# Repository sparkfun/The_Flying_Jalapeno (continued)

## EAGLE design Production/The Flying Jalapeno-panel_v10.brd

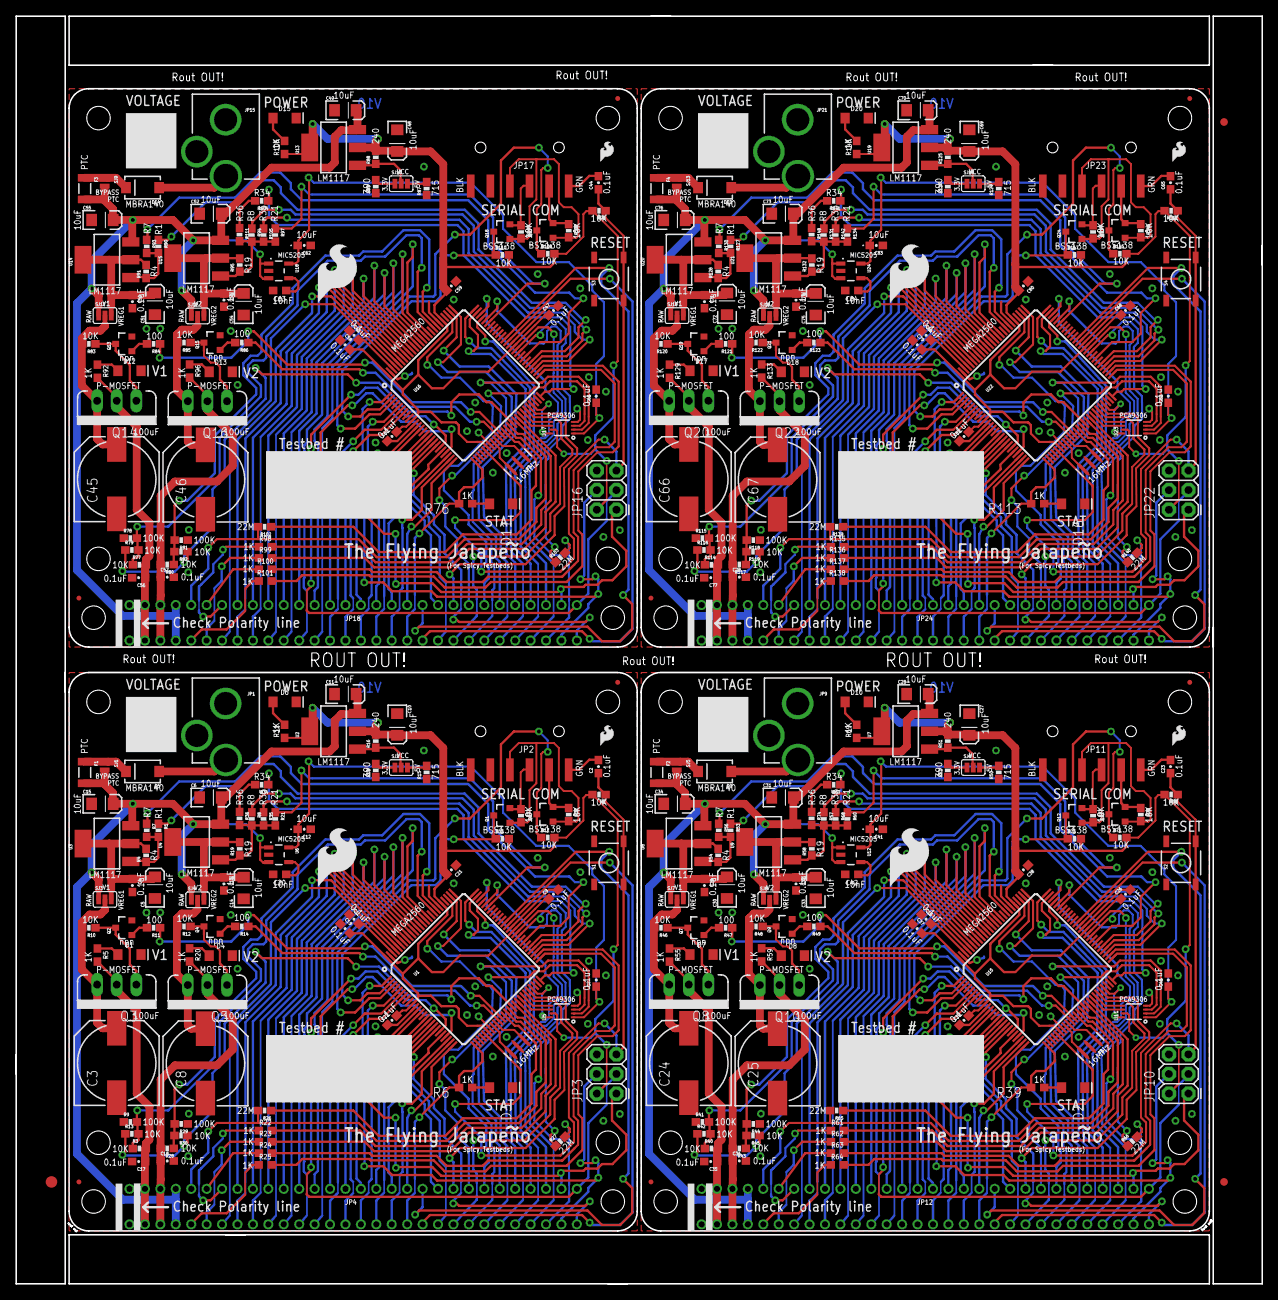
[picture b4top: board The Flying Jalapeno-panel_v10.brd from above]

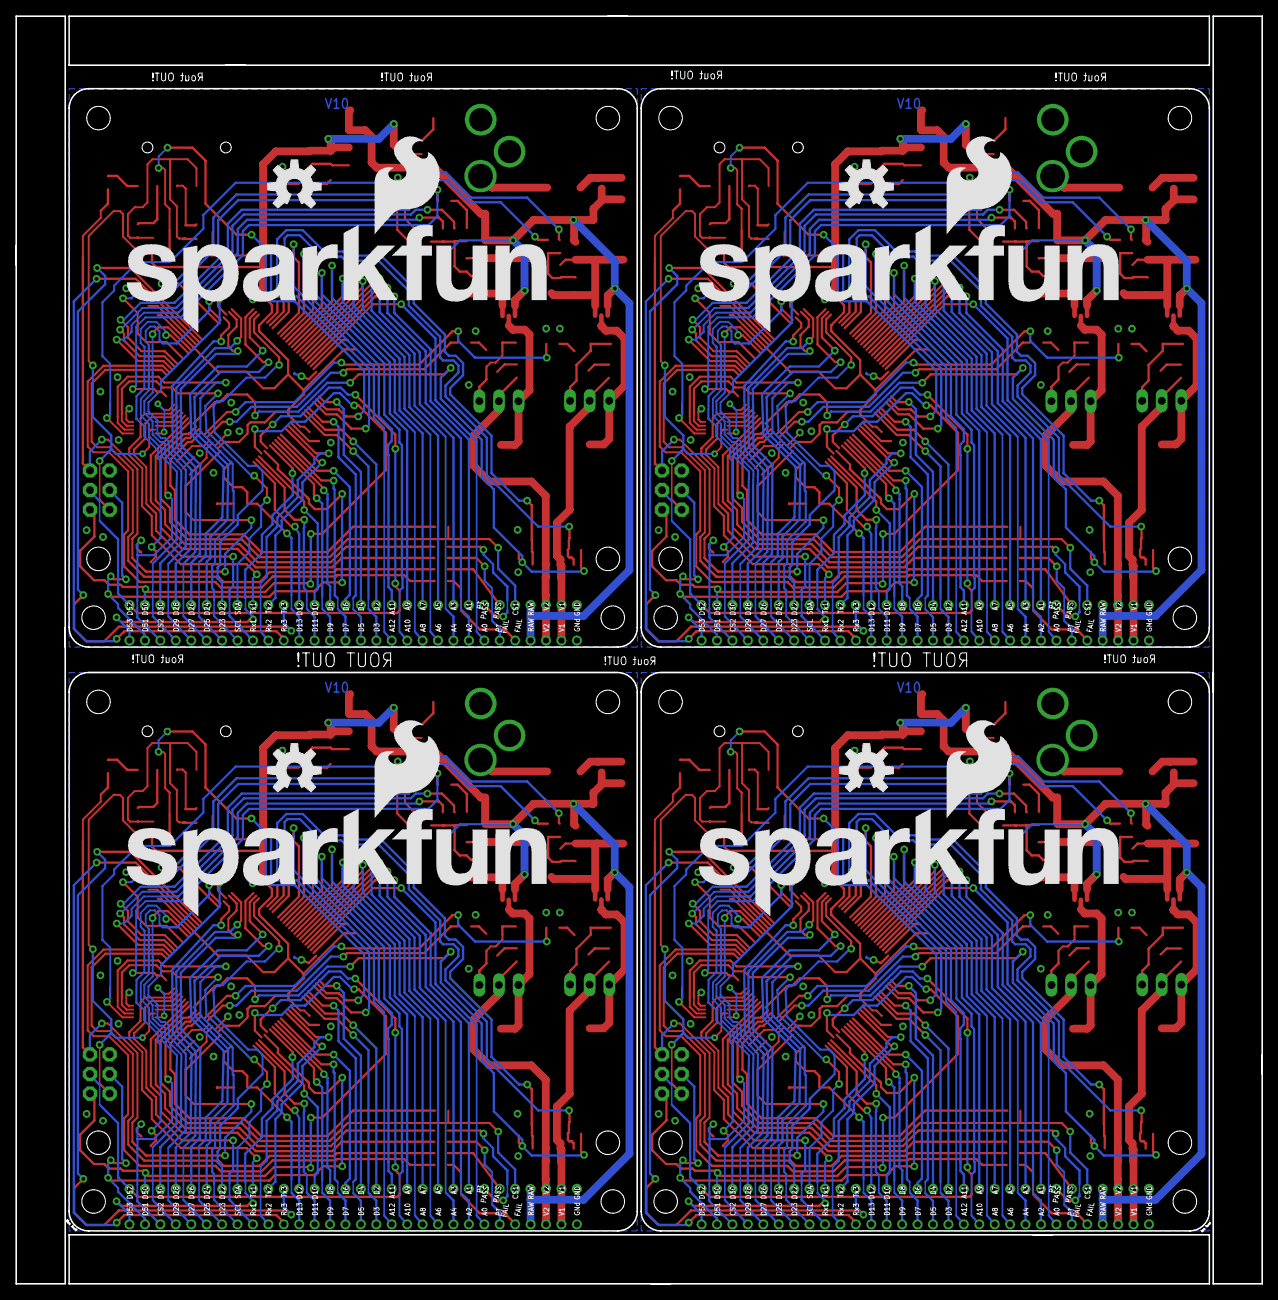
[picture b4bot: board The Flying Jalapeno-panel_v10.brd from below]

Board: 2 copper layers, 161.5 x 164.3 mm, 387 parts (8 on the bottom side), 436 nets.

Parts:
C1, C2, C4, C7, C9, C13, C16, C17, C18, C19, C21, C22, C23, C26, C29, C32, C35, C36, C37, C38, C39, C40, C43, C44, C47, C50, C53, C56, C57, C58, C59, C60, C61, C64, C65, C68, C71, C74, C77, C78, C79, C80, C81, C82: 0.1uF; 0603-CAP
C3, C8, C24, C25, C45, C46, C66, C67: 100uF; NIC_10X10.5_CAP
C5, C6, C10, C11, C14, C15, C27, C28, C30, C31, C33, C34, C48, C49, C51, C52, C54, C55, C69, C70, C72, C73, C75, C76: 10uF; EIA3216
C12, C41, C62, C83: 10uF; 0603-POL
C20, C42, C63, C84: 10nF; 0603
D1, D2, D3, D4, D6, D7, D8, D10, D11, D12, D13, D15, D16, D17, D18, D20: RED; LED-1206
D5, D9, D14, D19: MBRA140; SMA-DIODE
E$1: FIDUCIAL-1.5X3
E$7, E$8: FIDUCIAL-1X2
F1, F2, F3, F4: PTC-1206
JP1, JP9, JP15, JP21: 7V; POWER_JACK_PTH_LOCK
JP2, JP11, JP17, JP23: FTDI; FTDI_DEVICE_RA_SMT
JP3, JP10, JP16, JP22: 2X3
JP4, JP12, JP18, JP24: 2x30 RA FEMALE HEADER; FLYING_JALAPENO_V2_F
JP5, JP6, JP7, JP8, JP13, JP14, JP19, JP20: FIDUCIALUFIDUCIAL; MICRO-FIDUCIAL
LOGO1, LOGO5, LOGO9, LOGO13: SFE_LOGO_NAME_FLAME.5_INCH; SFE_LOGO_NAME_FLAME_.5
LOGO2, LOGO8, LOGO12, LOGO16: SFE_LOGO_FLAME.3_INCH; SFE_LOGO_FLAME_.3
LOGO3, LOGO6, LOGO10, LOGO14: SFE_LOGO_FLAME.1_INCH; SFE_LOGO_FLAME_.1
LOGO4, LOGO7, LOGO11, LOGO15: OSHW-LOGOL; OSHW-LOGO-L
Q1, Q6, Q11, Q12, Q17, Q18, Q23, Q24: BSS138, 200mA/50V; SOT23-3
Q2, Q4, Q7, Q9, Q13, Q15, Q19, Q21: MMBT2222A; SOT23-3
Q3, Q5, Q8, Q10, Q14, Q16, Q20, Q22: NDP6020P; TO220V
R1, R15, R21, R50, R53, R60, R87, R90, R97, R124, R127, R134: 715; 0603-RES
R2, R3, R10, R12, R13, R17, R28, R30, R32, R33, R37, R38, R40, R42, R43, R45, R46, R48, R70, R71, R72, R73, R75, R77, R79, R80, R82, R83, R85, R107, R108, R109, R110, R112, R114, R116, R117, R119, R120, R122, R144, R145, R146, R147: 10K; 0603-RES
R4, R16, R19, R51, R54, R58, R88, R91, R95, R125, R128, R132: 240; 0603-RES
R5, R6, R20, R22, R23, R24, R25, R31, R39, R55, R59, R61, R62, R63, R64, R69, R76, R92, R96, R98, R99, R100, R101, R106, R113, R129, R133, R135, R136, R137, R138, R143: 1k; 0603
R7, R8, R18, R52, R56, R57, R89, R93, R94, R126, R130, R131: 390; 0603-RES
R9, R29, R41, R44, R78, R81, R115, R118: 100k; 0603-RES
R11, R14, R34, R47, R49, R67, R84, R86, R104, R121, R123, R141: 100; 0603-RES
R26, R27, R65, R66, R102, R103, R139, R140: 22M; 0603-RES
R35, R36, R68, R74, R105, R111, R142, R148: 470; 0603-RES
S1, S2, S3, S4: TACTILE-SWITCH-SMD
SJ1, SJ5, SJ9, SJ13: PTC Bypass; PAD-JUMPER-2-NO_NO_SILK
SJ2, SJ3, SJ4, SJ6, SJ7, SJ8, SJ10, SJ11, SJ12, SJ14, SJ15, SJ16: PAD-JUMPER-3-2OF3_NC_BY_PASTE_YES_SILK_FULL_BOX
STANDOFF1, STANDOFF2, STANDOFF3, STANDOFF4, STANDOFF5, STANDOFF6, STANDOFF7, STANDOFF8, STANDOFF9, STANDOFF10, STANDOFF11, STANDOFF12, STANDOFF13, STANDOFF14, STANDOFF15, STANDOFF16: STAND-OFFTIGHT; STAND-OFF-TIGHT
U1, U10, U16, U22: ATMEGA2560AU; TQFP100
U2, U3, U4, U7, U8, U9, U13, U14, U15, U19, U20, U21: LM1117; SOT223
U5, U11, U17, U23: PCA9306; PCA9306DC-1:1
U6, U12, U18, U24: 3.3V MIC5205; SOT23-5
Y1, Y2, Y3, Y4: 16MHZ; RESONATOR-SMD

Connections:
3.3V: C7.1, C12.A, U5.1, U6.5
3.3V1: C40.1, C41.A, U11.1, U12.5
3.3V2: C61.1, C62.A, U17.1, U18.5
3.3V3: C82.1, C83.A, U23.1, U24.5
31/CAPRETURN1: R66.1, U10.59
31/CAPRETURN2: R27.1, U1.59
31/CAPRETURN3: R103.1, U16.59
31/CAPRETURN4: R140.1, U22.59
33/V1_3.3V: R7.1, U1.57
33/V1_3.3V1: R56.1, U10.57
33/V1_3.3V2: R93.1, U16.57
33/V1_3.3V3: R130.1, U22.57
35/V1_5V: R1.1, U1.55
35/V1_5V1: R53.1, U10.55
35/V1_5V2: R90.1, U16.55
35/V1_5V3: R127.1, U22.55
36/V2_3.3V: R8.1, U1.54
36/V2_3.3V1: R57.1, U10.54
36/V2_3.3V2: R94.1, U16.54
36/V2_3.3V3: R131.1, U22.54
37/V2_3.7V: R35.1, U1.53
37/V2_3.7V1: R68.1, U10.53
37/V2_3.7V2: R105.1, U16.53
37/V2_3.7V3: R142.1, U22.53
38/V2_4.2V: R34.1, U1.50
38/V2_4.2V1: R67.1, U10.50
38/V2_4.2V2: R104.1, U16.50
38/V2_4.2V3: R141.1, U22.50
39/V2_5V: R21.1, U1.70
39/V2_5V1: R60.1, U10.70
39/V2_5V2: R97.1, U16.70
39/V2_5V3: R134.1, U22.70
40/FAIL: R25.2, U1.52
40/FAIL1: R64.2, U10.52
40/FAIL2: R101.2, U16.52
40/FAIL3: R138.2, U22.52
41/PASS: R24.2, U1.51
41/PASS1: R63.2, U10.51
41/PASS2: R100.2, U16.51
41/PASS3: R137.2, U22.51
42/PT_FAIL: R23.2, U1.42
42/PT_FAIL1: R62.2, U10.42
42/PT_FAIL2: R99.2, U16.42
42/PT_FAIL3: R136.2, U22.42
43/PT_PASS: R22.2, U1.41
43/PT_PASS1: R61.2, U10.41
43/PT_PASS2: R98.2, U16.41
43/PT_PASS3: R135.2, U22.41
44/PT_CTRL: R13.1, R30.1, U1.40
44/PT_CTRL1: R42.1, R45.1, U10.40
44/PT_CTRL2: R79.1, R82.1, U16.40
44/PT_CTRL3: R116.1, R119.1, U22.40
45/CAPSENSE1: JP4.5, R26.2, U1.39
45/CAPSENSE2: JP12.5, R65.2, U10.39
45/CAPSENSE3: JP18.5, R102.2, U16.39
45/CAPSENSE4: JP24.5, R139.2, U22.39
46/CAPSENSE1: JP12.58, R66.2, U10.38
46/CAPSENSE2: JP4.58, R27.2, U1.38
46/CAPSENSE3: JP18.58, R103.2, U16.38
46/CAPSENSE4: JP24.58, R140.2, U22.38
47/CAPRETURN1: R26.1, U1.37
47/CAPRETURN2: R65.1, U10.37
47/CAPRETURN3: R102.1, U16.37
47/CAPRETURN4: R139.1, U22.37
48/PWR_CTRL1: R11.1, U1.36
48/PWR_CTRL2: R47.1, U10.36
48/PWR_CTRL3: R84.1, U16.36
48/PWR_CTRL4: R121.1, U22.36
49/PWR_CTRL1: R49.1, U10.35
49/PWR_CTRL2: R14.1, U1.35
49/PWR_CTRL3: R86.1, U16.35
49/PWR_CTRL4: R123.1, U22.35
A0: JP4.37, U1.97
A1: JP4.8, U1.96
A2: JP4.38, U1.95
A3: JP4.9, U1.94
A4: JP4.39, U1.93
A5: JP4.10, U1.92
A6: JP4.40, U1.91
A7: JP4.11, U1.90
A8: JP4.41, U1.89
A9: JP4.12, U1.88
A10: JP4.42, U1.87
A11: JP4.13, U1.86
A12: JP4.43, U1.85
A13: JP12.10, U10.92
A14: JP12.39, U10.93
A14/PT_READ_V1: R3.1, R9.2, R13.2, U1.83
A14/PT_READ_V2: R40.1, R41.2, R42.2, U10.83
A14/PT_READ_V3: R77.1, R78.2, R79.2, U16.83
A14/PT_READ_V4: R114.1, R115.2, R116.2, U22.83
A15: JP12.9, U10.94
A15/PT_READ_V1: R43.1, R44.2, R45.2, U10.82
A15/PT_READ_V2: R28.1, R29.2, R30.2, U1.82
A15/PT_READ_V3: R80.1, R81.2, R82.2, U16.82
A15/PT_READ_V4: R117.1, R118.2, R119.2, U22.82
A16: JP12.38, U10.95
A17: JP12.8, U10.96
A18: JP12.37, U10.97
A19: JP12.43, U10.85
A20: JP12.13, U10.86
A21: JP12.42, U10.87
A22: JP12.12, U10.88
A23: JP12.41, U10.89
A24: JP12.40, U10.91
A25: JP12.11, U10.90
A26: JP18.10, U16.92
A27: JP18.39, U16.93
A28: JP18.9, U16.94
A29: JP18.38, U16.95
A30: JP18.8, U16.96
A31: JP18.37, U16.97
A32: JP18.43, U16.85
A33: JP18.13, U16.86
A34: JP18.42, U16.87
A35: JP18.12, U16.88
A36: JP18.41, U16.89
A37: JP18.40, U16.91
A38: JP18.11, U16.90
A39: JP24.10, U22.92
A40: JP24.39, U22.93
A41: JP24.9, U22.94
A42: JP24.38, U22.95
A43: JP24.8, U22.96
A44: JP24.37, U22.97
A45: JP24.43, U22.85
A46: JP24.13, U22.86
A47: JP24.42, U22.87
A48: JP24.12, U22.88
A49: JP24.41, U22.89
A50: JP24.40, U22.91
A51: JP24.11, U22.90
AREF: C1.2, U1.98
AREF1: C16.2, U10.98
AREF2: C43.2, U16.98
AREF3: C64.2, U22.98
D1: JP12.47, U10.18
D2: JP4.14, U1.6
D3: JP4.44, U1.7
D4: JP4.15, U1.1
D5: JP4.45, U1.5
D6: JP4.16, U1.15
D7: JP4.46, U1.16
D8: JP4.17, U1.17
D9: JP4.47, U1.18
D10: JP4.18, U1.23
D11: JP4.48, U1.24
D12: JP4.19, U1.25
D13: JP4.49, R6.1, U1.26
D14: JP12.17, U10.17
D15: JP12.46, U10.16
D16: JP12.16, U10.15
D17: JP12.15, U10.1
D18: JP12.45, U10.5
D19: JP12.14, U10.6
D20: JP12.44, U10.7
D21: JP12.28, U10.60
D22: JP4.24, U1.78
D23: JP4.54, U1.77
D24: JP4.25, U1.76
D25: JP4.55, U1.75
D26: JP4.26, U1.74
D27: JP4.56, U1.73
D28: JP4.27, U1.72
D29: JP4.57, U1.71
D30: JP4.28, U1.60
D31: JP12.18, U10.23
D32: JP12.48, U10.24
D33: JP12.19, U10.25
D34: JP12.49, R39.1, U10.26
D35: JP12.24, U10.78
D36: JP12.25, U10.76
D37: JP12.55, U10.75
D38: JP12.26, U10.74
D39: JP12.56, U10.73
D40: JP12.27, U10.72
D41: JP12.57, U10.71
D42: JP12.54, U10.77
D43: JP18.47, U16.18
D44: JP18.17, U16.17
D45: JP18.46, U16.16
D46: JP18.16, U16.15
D47: JP18.15, U16.1
D48: JP18.45, U16.5
D49: JP18.14, U16.6
D50: JP18.44, U16.7
D51: JP18.28, U16.60
D52: JP18.18, U16.23
D53: JP18.48, U16.24
D54: JP18.19, U16.25
D55: JP18.49, R76.1, U16.26
D56: JP18.24, U16.78
D57: JP18.25, U16.76
D58: JP18.55, U16.75
D59: JP18.26, U16.74
D60: JP18.56, U16.73
D61: JP18.27, U16.72
D62: JP18.57, U16.71
D63: JP18.54, U16.77
D64: JP24.47, U22.18
D65: JP24.17, U22.17
D66: JP24.46, U22.16
D67: JP24.16, U22.15
D68: JP24.15, U22.1
D69: JP24.45, U22.5
D70: JP24.14, U22.6
D71: JP24.44, U22.7
D72: JP24.28, U22.60
D73: JP24.18, U22.23
D74: JP24.48, U22.24
D75: JP24.19, U22.25
D76: JP24.49, R113.1, U22.26
D77: JP24.24, U22.78
D78: JP24.25, U22.76
D79: JP24.55, U22.75
D80: JP24.26, U22.74
D81: JP24.56, U22.73
D82: JP24.27, U22.72
D83: JP24.57, U22.71
D84: JP24.54, U22.77
DTR: C2.2, JP2.1
DTR1: C23.2, JP11.1
DTR2: C44.2, JP17.1
DTR3: C65.2, JP23.1
EN_I2C: U1.47, U5.8
EN_I2C1: U10.47, U11.8
EN_I2C2: U16.47, U17.8
EN_I2C3: U22.47, U23.8
FTDI_VCC: JP2.4, Q1.1, Q6.1, R32.2, R37.2
FTDI_VCC1: JP11.4, Q11.1, Q12.1, R70.2, R72.2
FTDI_VCC2: JP17.4, Q17.1, Q18.1, R107.2, R109.2
FTDI_VCC3: JP23.4, Q23.1, Q24.1, R144.2, R146.2
GND: C1.1, C3.-, C4.2, C5.C, C6.C, C7.2, C8.-, C9.2, C10.C, C11.C, C12.K, C13.2, C14.C, C15.C, C17.2, C18.2, C19.1, C20.2, C21.1, C22.1, D1.C, D3.C, D4.C, D6.C, JP1.GND, JP1.GNDBREAK, JP2.5, JP2.6, JP3.6, JP4.1, JP4.31, Q2.2, Q4.2, R9.1, R15.1, R18.1, R29.1, S1.1, S1.2, U1.11, U1.32, U1.62, U1.81, U1.99, U5.4, U6.2, Y1.2
GND1: C16.1, C24.-, C25.-, C26.2, C27.C, C28.C, C29.2, C30.C, C31.C, C32.2, C33.C, C34.C, C35.2, C36.2, C37.1, C38.1, C39.1, C40.2, C41.K, C42.2, D2.C, D7.C, D8.C, D10.C, JP9.GND, JP9.GNDBREAK, JP10.6, JP11.5, JP11.6, JP12.1, JP12.31, Q7.2, Q9.2, R41.1, R44.1, R50.1, R52.1, S2.1, S2.2, U10.11, U10.32, U10.62, U10.81, U10.99, U11.4, U12.2, Y2.2
GND2: C43.1, C45.-, C46.-, C47.2, C48.C, C49.C, C50.2, C51.C, C52.C, C53.2, C54.C, C55.C, C56.2, C57.2, C58.1, C59.1, C60.1, C61.2, C62.K, C63.2, D11.C, D12.C, D13.C, D15.C, JP15.GND, JP15.GNDBREAK, JP16.6, JP17.5, JP17.6, JP18.1, JP18.31, Q13.2, Q15.2, R78.1, R81.1, R87.1, R89.1, S3.1, S3.2, U16.11, U16.32, U16.62, U16.81, U16.99, U17.4, U18.2, Y3.2
GND3: C64.1, C66.-, C67.-, C68.2, C69.C, C70.C, C71.2, C72.C, C73.C, C74.2, C75.C, C76.C, C77.2, C78.2, C79.1, C80.1, C81.1, C82.2, C83.K, C84.2, D16.C, D17.C, D18.C, D20.C, JP21.GND, JP21.GNDBREAK, JP22.6, JP23.5, JP23.6, JP24.1, JP24.31, Q19.2, Q21.2, R115.1, R118.1, R124.1, R126.1, S4.1, S4.2, U22.11, U22.32, U22.62, U22.81, U22.99, U23.4, U24.2, Y4.2
unnamed: R34.2, R36.1
unnamed: U1.44, U5.5
unnamed: R16.1, SJ2.2, U2.1
unnamed: D3.A, R6.2
unnamed: D1.A, R5.1
unnamed: JP4.7, R22.1
unnamed: JP4.36, R23.1
unnamed: Q2.1, R11.2
unnamed: R1.2, R4.1, R7.2, U3.1
unnamed: R8.2, R19.1, R21.2, R35.2, R36.2, U4.1
unnamed: D4.A, R20.1
unnamed: Q2.3, Q3.1, R10.1
unnamed: Q4.1, R14.2
unnamed: Q4.3, Q5.1, R12.1
unnamed: D5.C, F1.1, SJ1.1
unnamed: JP2.3, Q1.2, R32.1
unnamed: R18.2, SJ2.1
unnamed: R15.2, SJ2.3
unnamed: JP4.6, R24.1
unnamed: JP4.35, R25.1
unnamed: C4.1, C5.A, R4.2, SJ3.3, U3.2, U3.4
unnamed: C3.+, Q3.3, R10.2, SJ3.2
unnamed: C8.+, Q5.3, R12.2, SJ4.2
unnamed: D5.A, JP1.PWR
unnamed: D6.A, R31.2
unnamed: JP2.2, Q6.2, R37.1
unnamed: U1.43, U5.6
unnamed: C20.1, U6.4
unnamed: Q7.1, R47.2
unnamed: Q7.3, Q8.1, R46.1
unnamed: Q9.1, R49.2
unnamed: Q9.3, Q10.1, R48.1
unnamed: D9.C, F2.1, SJ5.1
unnamed: R51.1, SJ6.2, U7.1
unnamed: R52.2, SJ6.1
unnamed: R50.2, SJ6.3
unnamed: D7.A, R55.1
unnamed: R53.2, R54.1, R56.2, U8.1
unnamed: R57.2, R58.1, R60.2, R68.2, R74.2, U9.1
unnamed: D8.A, R59.1
unnamed: C29.1, C30.A, R54.2, SJ7.3, U8.2, U8.4
unnamed: C24.+, Q8.3, R46.2, SJ7.2
unnamed: C25.+, Q10.3, R48.2, SJ8.2
unnamed: D9.A, JP9.PWR
unnamed: U10.33, Y2.3
unnamed: U10.34, Y2.1
unnamed: D2.A, R39.2
unnamed: JP12.7, R61.1
unnamed: JP12.36, R62.1
unnamed: JP12.6, R63.1
unnamed: JP12.35, R64.1
unnamed: D10.A, R69.2
unnamed: JP11.3, Q12.2, R72.1
unnamed: JP11.2, Q11.2, R70.1
unnamed: R67.2, R74.1
unnamed: U10.44, U11.5
unnamed: U10.43, U11.6
unnamed: C42.1, U12.4
unnamed: Q13.1, R84.2
unnamed: Q13.3, Q14.1, R83.1
unnamed: Q15.1, R86.2
unnamed: Q15.3, Q16.1, R85.1
unnamed: D14.C, F3.1, SJ9.1
unnamed: R88.1, SJ10.2, U13.1
unnamed: R89.2, SJ10.1
unnamed: R87.2, SJ10.3
unnamed: D12.A, R92.1
unnamed: R90.2, R91.1, R93.2, U14.1
unnamed: R94.2, R95.1, R97.2, R105.2, R111.2, U15.1
unnamed: D13.A, R96.1
unnamed: C50.1, C51.A, R91.2, SJ11.3, U14.2, U14.4
unnamed: C45.+, Q14.3, R83.2, SJ11.2
unnamed: U1.33, Y1.3
unnamed: U1.34, Y1.1
unnamed: C46.+, Q16.3, R85.2, SJ12.2
unnamed: D14.A, JP15.PWR
unnamed: U16.33, Y3.3
unnamed: U16.34, Y3.1
unnamed: D11.A, R76.2
unnamed: JP18.7, R98.1
unnamed: JP18.36, R99.1
unnamed: JP18.6, R100.1
unnamed: JP18.35, R101.1
unnamed: D15.A, R106.2
unnamed: JP17.3, Q18.2, R109.1
unnamed: JP17.2, Q17.2, R107.1
unnamed: R104.2, R111.1
unnamed: U16.44, U17.5
unnamed: U16.43, U17.6
unnamed: C63.1, U18.4
unnamed: Q19.1, R121.2
unnamed: Q19.3, Q20.1, R120.1
unnamed: Q21.1, R123.2
unnamed: Q21.3, Q22.1, R122.1
unnamed: D19.C, F4.1, SJ13.1
unnamed: R125.1, SJ14.2, U19.1
unnamed: R126.2, SJ14.1
unnamed: R124.2, SJ14.3
unnamed: D17.A, R129.1
unnamed: R127.2, R128.1, R130.2, U20.1
unnamed: R131.2, R132.1, R134.2, R142.2, R148.2, U21.1
unnamed: D18.A, R133.1
unnamed: C71.1, C72.A, R128.2, SJ15.3, U20.2, U20.4
unnamed: C66.+, Q20.3, R120.2, SJ15.2
unnamed: C67.+, Q22.3, R122.2, SJ16.2
unnamed: D19.A, JP21.PWR
unnamed: U22.33, Y4.3
unnamed: U22.34, Y4.1
unnamed: D16.A, R113.2
unnamed: JP24.7, R135.1
unnamed: JP24.36, R136.1
unnamed: JP24.6, R137.1
unnamed: JP24.35, R138.1
unnamed: D20.A, R143.2
unnamed: JP23.3, Q24.2, R146.1
unnamed: JP23.2, Q23.2, R144.1
unnamed: R141.2, R148.1
unnamed: U22.44, U23.5
unnamed: U22.43, U23.6
unnamed: C84.1, U24.4
PB0: JP4.60, U1.19
PB1: JP3.3, JP4.30, U1.20
PB2: JP3.4, JP4.59, U1.21
PB3: JP3.1, JP4.29, U1.22
PB4: JP12.60, U10.19
PB5: JP10.3, JP12.30, U10.20
PB6: JP10.4, JP12.59, U10.21
PB7: JP10.1, JP12.29, U10.22
PB8: JP18.60, U16.19
PB9: JP16.3, JP18.30, U16.20
PB10: JP16.4, JP18.59, U16.21
PB11: JP16.1, JP18.29, U16.22
PB12: JP24.60, U22.19
PB13: JP22.3, JP24.30, U22.20
PB14: JP22.4, JP24.59, U22.21
PB15: JP22.1, JP24.29, U22.22
RAW: C6.A, C11.A, C15.A, F1.2, JP4.4, JP4.34, SJ1.2, SJ3.1, SJ4.1, U2.3, U3.3, U4.3, U6.1, U6.3
RAW1: C28.A, C31.A, C34.A, F2.2, JP12.4, JP12.34, SJ5.2, SJ7.1, SJ8.1, U7.3, U8.3, U9.3, U12.1, U12.3
RAW2: C49.A, C52.A, C55.A, F3.2, JP18.4, JP18.34, SJ9.2, SJ11.1, SJ12.1, U13.3, U14.3, U15.3, U18.1, U18.3
RAW3: C70.A, C73.A, C76.A, F4.2, JP24.4, JP24.34, SJ13.2, SJ15.1, SJ16.1, U19.3, U20.3, U21.3, U24.1, U24.3
RESET: C2.1, JP3.5, R2.1, S1.3, S1.4, U1.30
RESET1: C23.1, JP10.5, R38.1, S2.3, S2.4, U10.30
RESET2: C44.1, JP16.5, R75.1, S3.3, S3.4, U16.30
RESET3: C65.1, JP22.5, R112.1, S4.3, S4.4, U22.30
RX0: Q1.3, R33.1, U1.2
RX1: JP4.52, U1.45
RX2: JP4.51, U1.12
RX3: JP4.50, U1.63
RX4: JP12.50, U10.63
RX5: JP12.51, U10.12
RX6: Q12.3, R73.1, U10.2
RX7: JP12.52, U10.45
RX8: JP18.50, U16.63
RX9: JP18.51, U16.12
RX10: Q18.3, R110.1, U16.2
RX11: JP18.52, U16.45
RX12: JP24.50, U22.63
RX13: JP24.51, U22.12
RX14: Q24.3, R147.1, U22.2
RX15: JP24.52, U22.45
SCL1: JP4.53, U5.2
SCL2: JP12.53, U11.2
SCL3: JP18.53, U17.2
SCL4: JP24.53, U23.2
SDA1: JP4.23, U5.3
SDA2: JP12.23, U11.3
SDA3: JP18.23, U17.3
SDA4: JP24.23, U23.3
TX0: Q6.3, R17.1, U1.3
TX1: JP4.22, U1.46
TX2: JP4.21, U1.13
TX3: JP4.20, U1.64
TX4: JP12.20, U10.64
TX5: JP12.21, U10.13
TX6: JP12.22, U10.46
TX7: Q11.3, R71.1, U10.3
TX8: JP18.20, U16.64
TX9: JP18.21, U16.13
TX10: JP18.22, U16.46
TX11: Q17.3, R108.1, U16.3
TX12: JP24.20, U22.64
TX13: JP24.21, U22.13
TX14: JP24.22, U22.46
TX15: Q23.3, R145.1, U22.3
V1: C17.1, JP4.2, JP4.32, Q3.2, R3.2, R5.2
V2: C18.1, JP4.3, JP4.33, Q5.2, R20.2, R28.2
V3: C35.1, JP12.2, JP12.32, Q8.2, R40.2, R55.2
V4: C36.1, JP12.3, JP12.33, Q10.2, R43.2, R59.2
V5: C56.1, JP18.2, JP18.32, Q14.2, R77.2, R92.2
V6: C57.1, JP18.3, JP18.33, Q16.2, R80.2, R96.2
V7: C77.1, JP24.2, JP24.32, Q20.2, R114.2, R129.2
V8: C78.1, JP24.3, JP24.33, Q22.2, R117.2, R133.2
VCC: C9.1, C10.A, C19.2, C21.2, C22.2, JP3.2, R2.2, R16.2, R17.2, R31.1, R33.2, U1.10, U1.31, U1.61, U1.80, U1.100, U2.2, U2.4, U5.7
VCC1: C26.1, C27.A, C37.2, C38.2, C39.2, JP10.2, R38.2, R51.2, R69.1, R71.2, R73.2, U7.2, U7.4, U10.10, U10.31, U10.61, U10.80, U10.100, U11.7
VCC2: C47.1, C48.A, C58.2, C59.2, C60.2, JP16.2, R75.2, R88.2, R106.1, R108.2, R110.2, U13.2, U13.4, U16.10, U16.31, U16.61, U16.80, U16.100, U17.7
VCC3: C68.1, C69.A, C79.2, C80.2, C81.2, JP22.2, R112.2, R125.2, R143.1, R145.2, R147.2, U19.2, U19.4, U22.10, U22.31, U22.61, U22.80, U22.100, U23.7
VREG2OUT: C13.1, C14.A, R19.2, SJ4.3, U4.2, U4.4
VREG2OUT1: C32.1, C33.A, R58.2, SJ8.3, U9.2, U9.4
VREG2OUT2: C53.1, C54.A, R95.2, SJ12.3, U15.2, U15.4
VREG2OUT3: C74.1, C75.A, R132.2, SJ16.3, U21.2, U21.4

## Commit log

2015-06-05 adding in gitignore and readme
2015-06-05 added in v01 of eagle design
2015-06-05 Power input Diode
2015-06-05 Some PROD_IDS and moved to 100uF SMD caps
2015-06-05 more PROD_IDs
2015-06-05 more prod ids
2015-06-05 more prod ids and some sch cleanup
    last thing that needs prod ids is the headers at the bottom, not sure if
    we're gonna go with break away or combining 10pin and 8pin pieces
2015-06-17 pulled libraries to get lost devices
    Still re-thinking connector, might go with 2x20 RA M/F
2015-07-02 Starting the arduino library
    Still has some left over stuff from the Morse Code example I started
    from. Basic stuff is in there though, and it's ready to grow - wahoo!
2015-07-09 Moved to Mega2560 and 2x30 2mm connector
    device and packages for the 2x30 connector all live in the "local"
    sparkfun.lbr for now. I will push to testing.lbr soon.
2015-07-09 trace cleanup
2015-07-13 Modified Capsense pad device to use only 1 pin/pad
    I realized that I don't need the usual two lines for capsense buttons on
    this (SEND/RETURN). Because the resistors are going to live on the
    board, then the "button" on the testbed is only an extension of one net.
    Updated library devices to reflect this correction.
2015-07-13 Cleaning up repo - deleting local libraries
    I commited the FJ device and new capsense to the testing library repo,
    and so no longer need them in here.
2015-07-14 finalized resistor values on lipo fake out vreg
2015-07-14 Added labels to 2x30 connector
    also a lot of other small stuff as I went through the checklist
2015-07-14 added labels to all parts
2015-07-28 Fixed Rogue trace off of capsense2
    Thanks for catching this in your review Kade!
2015-07-29 created bracket for mounting flaying jalapeno to testbeds
2015-11-25 Added setV1() and setV2() for controlling high side switches
    -note, you can actually set the output voltage on each vreg using these
    functions.
    -Added capsense include to example FJ1. This example sketch still needs
    a lot of standard stuff included.
2016-03-17 adding some pass/fail led functionality
    setup as outpus automatically in initialise function.
    also fixed some power control functions.
    added some defines for LEDs in header file
2016-05-20 added in PCA9306 for I2C - still not netted or routed
    also added ignore for lock files
2016-06-03 Placed/routed the PCA9306 into the design
    Still some silk labeling to do, and check that GND pours are as good as
    they can flow.
2016-06-06 finished up routing and adjusted silk
    Added/updated silk to:
    Led resistors (stat and 4 others)- now are 1K
    MIC5205 3.3V vreg
    10uF pol cap
    10nF bypass cap - near vreg
    PCA9306
2016-06-06 removed RAW split test, moved pwr led from io to VCC
2016-06-06 moved test bed # silk and box back into position
2016-06-06 moved V1 and V2 leds resistors to 1K
    also update silk labeling
    also removed test point on 3.3V vreg output
2016-06-06 removed bottom silk for optional I2C pullups
    They are no longer on this design, I will rely on internal pullups, or
    if the product has them, that should be good too.
2016-06-06 cleaning up some routing
2016-06-06 Added measures
2016-06-06 added prod id part for smd 6 pin header (ftdi)
2016-06-09 fixed rx/tx trace overlap problem
    I had previously swapped out the device for the newest version with PROD
    ID and it messed with my pin assignments resulting in changing copper. I
    assumed it wouldn't effect copper and failed to run the DRC again. Sorry
    I didn't see this before requesting a review.
2016-06-14 added PROD_ID to FJ connector (JP4)
2016-07-26 Adding in production testing stuff
    self test sketch and dummy hardware
2016-07-27 added test_part1_result to indicate complete success
    Now the part1 (IO and led lines) must pass, and then part2 (analog pins)
    must pass for the STAT LED to come on solid - indicating TOTAL success
    of all tests.
2016-07-27 library work: default to 3.3V on vregs (even when off)
    Also added delay_time vairalbe to slow down testing for DMM readings
2016-07-28 corrected Resistor names
    Some resistor names skipped in the 30s, now they increment correctly.
2016-07-28 Switched to reference designators on resistors near adjustable vregs
    These values may change for special testbeds, and so an "R#" is more
    correct, and easier to reference the schematic.
2016-07-28 enlarged the "testbed #" silk box
2016-07-28 Exported libraries from SCH
2016-07-28 Modified FJ female connector package
    Turns out the legs are narrower than the data sheet says. They come
    straight down off the sides of the plastic molding. Wynn noticed this
    when he built up the prototypes. I grabbed a sample and modified the
    package to fit more precisely. Also added a huge polarity mark.
2016-07-28 replaced updated connector package in design
2016-07-28 removed version number from eagle file name
2016-07-28 incremented version number to v10
    in sch and brd
    Had to nudge traces around when I replaced the fj connector for the
    updated package.
2016-07-28 added in PCA enable pin test
2016-07-28 Moved PCA_enable() into library - oh hell yeah!
2016-07-28 moved PCA_enable() to library
2016-07-28 schematic cleanup - fit all into one frame
2016-07-28 update red leds to correct part/prod_ids
2016-07-28 removed a small rouge trace off of RAW, must have been from v01
2016-07-28 small nudges to some traces to get nicer angles and removes some unnecessary kinks
2016-08-25 panel built
2016-09-01 changed delay time in analog read tests to 100
    for quicker testing. 100 ms is sufficient.
2016-09-01 added V1/V2 leds on at end of test
    also added TB EAGLE folder, moved dummy in there
2016-09-01 moved selftest code to TB CODE folder
2016-09-01 added programming jig eagle files
2016-09-01 Added cutouts in the PM to allow space for nylon standoffs
    had to mill these out on v01. Originally planned on testing without
    these populated.
2016-09-08 Programming stuff for use with Pi_grammer
    -contains bash files used on stand alone raspi programmer
    -separate bash files for fuse/boot/lock, and serial upload
    -contains bootloader hex and sefl-test hex
    -also has most current test.py python script. This will most likely get
    augmented, in the Pi_grammer repo, so don't trust this copy is up to
    date. visit repo for the latest and greatest:
2016-09-09 Changed "FJ Bracket" text to tplace
    also made the brd file have 8 copies, for quicker adding to QC panels
    when we order a tone of these.
2016-10-19 added -i delay to fuse programming, changed EXT_FUSE to FD
    to ensure proper speed for fresh chip.
    Mega2560 verifies a FD when you write an FD to ext fuse
2016-10-19 temporary manual testing of the PT circuit
    I will need to put this into another automated portion of the test (in
    the future), but to get through th IP, I just put this new code on, hit
    reset a few times, and jumpered V1 and V2 to GND verifying that the PT
    showed 486 correctly.
2016-11-01 added SPI names on pins in FJ symbol
    digital pins 50, 51, 52, 53 are aka MISO, MOSI, SCK, SS
2016-11-03 added in example test code
    simple starting point for most beds with the FJ. just pretest and test
    capsense.
2016-11-15 Adding comments. Renamed functions. Defined static pins. Autoformatted.
2016-11-15 Defined pins. Autoformat. Changed to standard variable naming conventions.
2016-11-15 Changing PCA to enablePCA(), disablePCA()
2016-11-15 Giving name to statLED in lib. Fixing example to use statusLED.
2016-11-15 Adding backwards compatibility to depricated functions
2016-11-15 Adding examples. Fixing bug in powerTest.
    PowerTest could not fail because of &&. Reading can not be both smaller and larger than jumper_val.
2016-11-15 Refactoring verifyVoltage() function to use floating voltage. Adding example.
2016-11-15 Adding keywords
2016-11-21 Updating Bracket design to use 0.11 drill hits
    to keep consistent with our QC panel drill summary for NPTH
2016-11-21 removing bracket SCH file
    unnecessary to keep this, no device/symbols for this, so just need brd
    file for ordering.
2016-11-21 removing local temp libraries
    The FJ device has been rolled into SFE testing library. I'd rather only
    keep it in one place, to avoid version control wackiness.
2016-11-22 "custom" pretest function - send it spcific pins
    When you need more pre-tests for shorts to ground, use this function. It
    allows you to send a control pin and read pin, and returns true if all
    is good (no jumper).
2017-01-07 verifyVoltage now works, fixed a few typos
2017-01-07 verifyVoltage now works
2017-01-23 Fixing my mods to map floats correctly
2017-02-15 Fixed bPlace silk labels on 2x30 header
    These used to overlap onto the pth headers cutting a lot of the silk.
    This fixes issue #7
    Also nudged some vias and traces to ensure none of the silk gets cut.
    Also bumped silk up to 0.032, 18% (previously was 0.026). This should
    look really nice on the next round of pcbs.
2017-02-15 changed version to v11, to keep things straight.
2017-02-16 cleaning up net naming convention on 48/49
    "48/PWR_CTRL_V1" and "49/PWR_CTRL_V2".
    issue #3
2017-02-17 Updated FJ device - symbol and package
    Symbol pins are now correctly named A0 and A1, they used to have A0/TX0
    and A1/RX0, which is incorrect and left over from the mega pro designs.
    Also, with this update to the device came a small update to the package.
    Only thing effected was the drill hits for the brackets are now the
    correct "tighter" size of 0.11".
2017-02-21 moved arduino library to it's own repo
    https://github.com/lewispg228/FlyingJalapeno
    For easier dev work. now you can clone into libraries folder directly.
2017-08-17 Deleting production testing stuff - moved to qcvault
    can be found in SUB-13059
2018-03-09 Quick change to font
2018-05-30 It begins
    Removed PCA, joined capsense return lines (less complexity on board), swapped V2 line and RAW line to seperate V1 and V2. I also decreased the width to 20 mils (down from 40) on V1/2 according to tra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
2018-06-01 Removed regulator, started rerouting
2018-06-01 smaller caps, capsense, ws2812's
    Smaller capacitors 10uf down from 100uf, added to lines preceding high side switch. I'll be rerouting Atmega to make sense of where the ws2812's and capsense will sit but wanted to sync before I do t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
2018-06-01 Header moved to right side
    Making some space for programming adapter.
